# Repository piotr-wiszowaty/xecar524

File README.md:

xecar524
========

An [Atari XL/XE](http://en.wikipedia.org/wiki/Atari_8-bit_family) flash cartridge
with a battery backed up R-Time 8 emulator. The device handles up to 4 Mbit,
3.3V, PLCC-32 flash memories (e.g. SST39VF010, SST39VF020, SST39VF040).

By default the base SDX image at `$00000` is loaded. Another cartridge image
may be switched to by using `CAR` command.

ROM Memory Map
--------------

* `$00000`..`$1FFFF` - SpartaDOS X 4.49, 128k (SDX449\_sdx128.rom)
* `$20000`..`$23FFF` - 043M OSS cartridge (e.g. MAC/65 1.00)
* `$24000`..`$27FFF` - 034M OSS cartridge (e.g. MAC-65 v1.02)
* `$28000`..`$2BFFF` - standard 16k cartridge
* `$2C000`..`$2DFFF` - standard 8k cartridge

Cartridge Selection
-------------------

The cartridge image to switch to is selected with jumpers:

* `CFG0`: off, `CFG1`: off - 043M OSS cartridge
* `CFG0`: on,  `CFG1`: off - 034M OSS cartridge
* `CFG0`: off, `CFG1`: on  - standard 16k cartridge
* `CFG0`: on,  `CFG1`: on  - standard 8k cartridge

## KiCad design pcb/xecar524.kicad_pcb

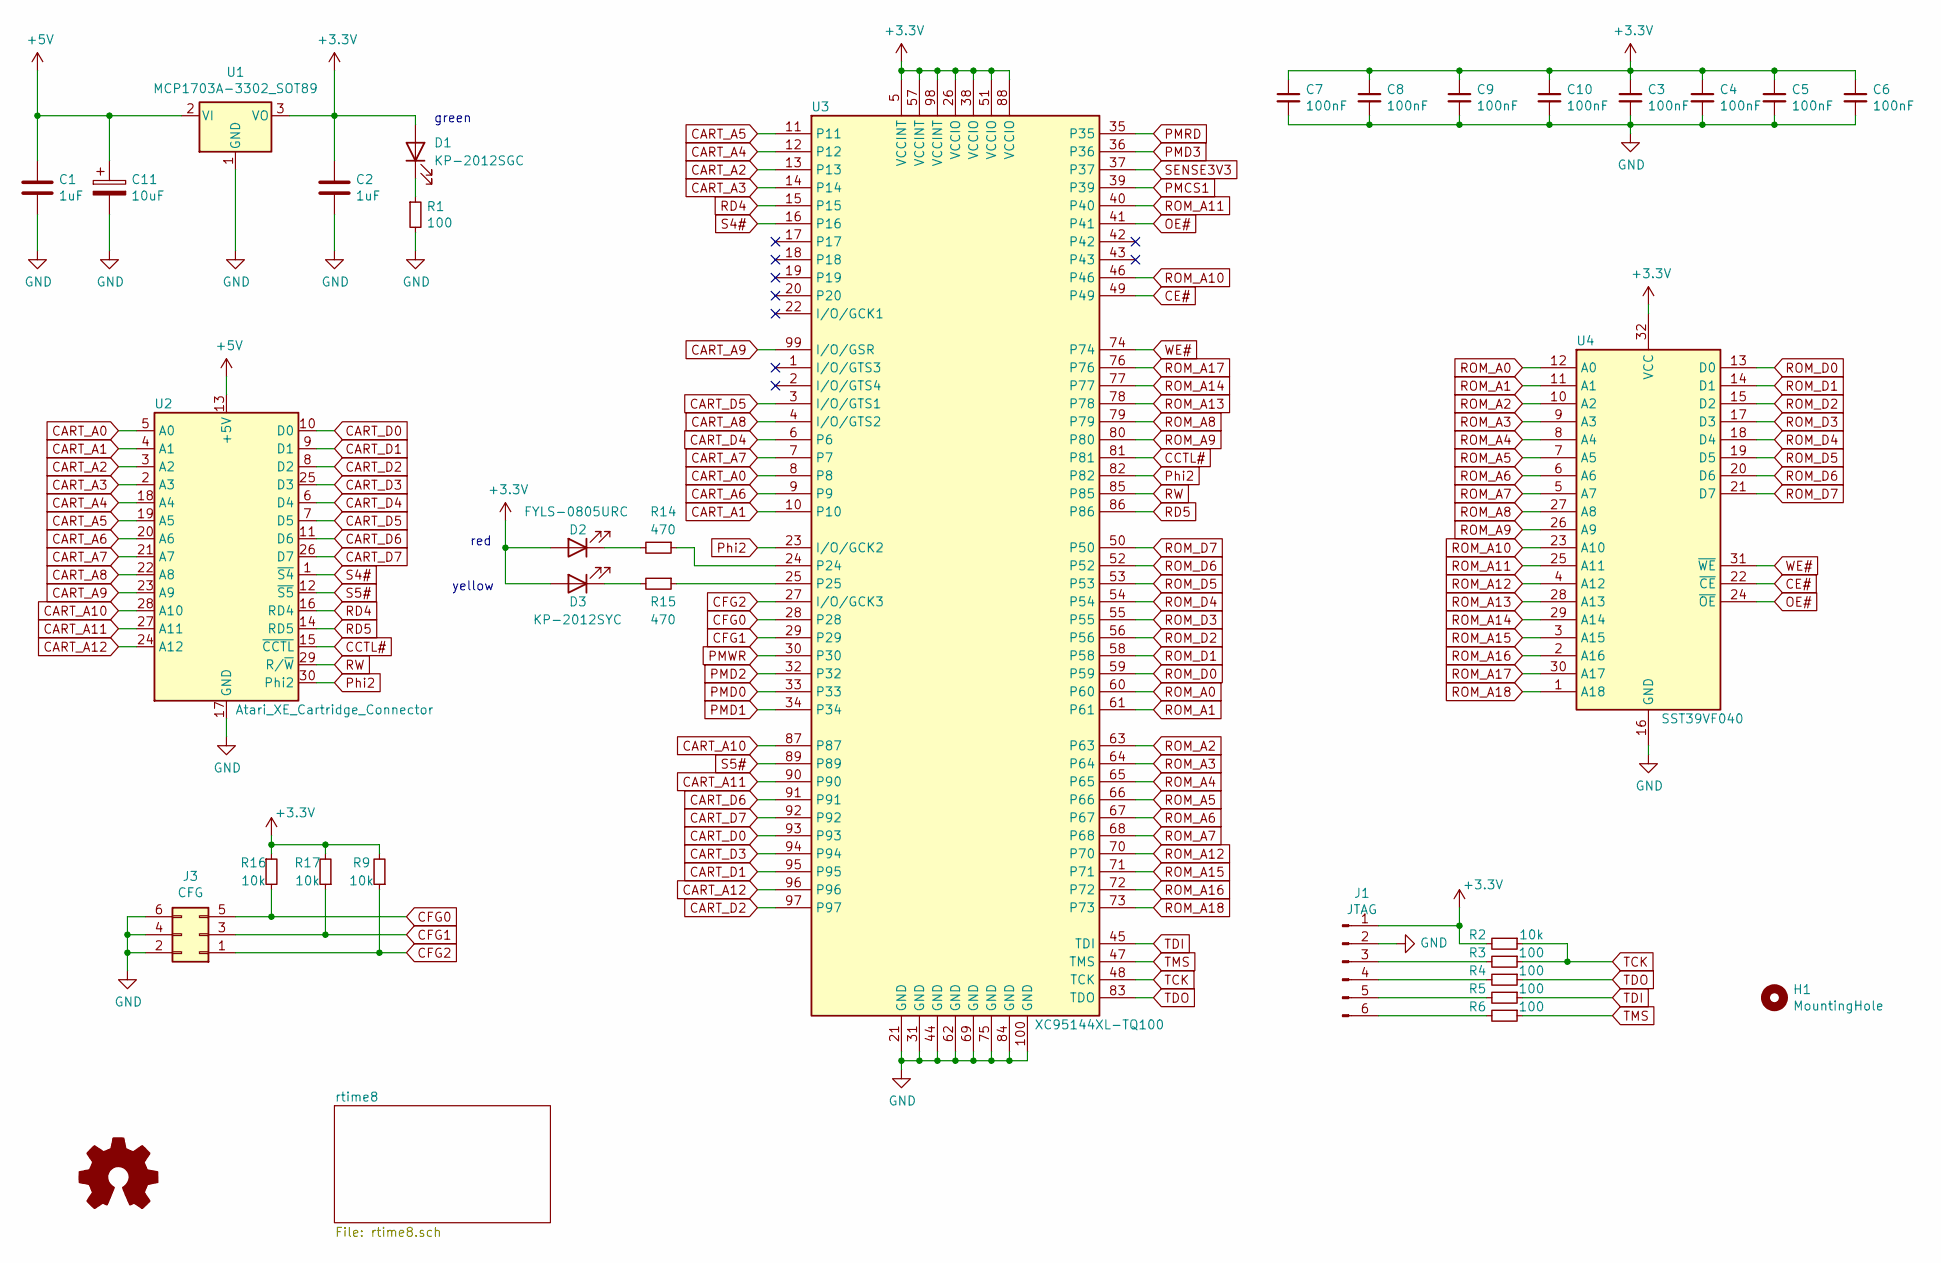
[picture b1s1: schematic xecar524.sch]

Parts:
C1, C2: 1uF; C_1206_3216Metric_Pad1.33x1.80mm_HandSolder
C3, C4, C5, C6, C7, C8, C9, C10: 100nF; C_0805_2012Metric_Pad1.18x1.45mm_HandSolder
C11: 10uF; CP_EIA-3528-12_Kemet-T_Pad1.50x2.35mm_HandSolder
D1: KP-2012SGC; D_0805_2012Metric_Pad1.15x1.40mm_HandSolder
D2: FYLS-0805URC; D_0805_2012Metric_Pad1.15x1.40mm_HandSolder
D3: KP-2012SYC; D_0805_2012Metric_Pad1.15x1.40mm_HandSolder
H1: MountingHole; MountingHole_5mm
J1: JTAG; PinHeader_1x06_P2.54mm_Horizontal_HighProfile
J3: CFG; PinHeader_2x03_P2.54mm_Horizontal
LOGO1: Logo_Open_Hardware_Small; OSHW-Symbol_8.9x8mm_Copper
R1, R3, R4, R5, R6: 100; R_0805_2012Metric_Pad1.20x1.40mm_HandSolder
R2, R9, R16, R17: 10k; R_0805_2012Metric_Pad1.20x1.40mm_HandSolder
R14, R15: 470; R_0805_2012Metric_Pad1.20x1.40mm_HandSolder
U1: MCP1703A-3302_SOT89; SOT-89-3
U2: Atari_XE_Cartridge_Connector
U3: XC95144XL-TQ100; TQFP-100_14x14mm_P0.5mm
U4: SST39VF040; PLCC-32_SMD-Socket

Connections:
+3V3: C2.1, C3.1, C4.1, C5.1, C6.1, C7.1, C8.1, C9.1, C10.1, D1.2 (A), D2.2 (A), D3.2 (A), J1.1, R2.2, R9.2, R16.1, R17.2, U1.3 (VO), U3.5 (VCCINT), U3.26 (VCCIO), U3.38 (VCCIO), U3.51 (VCCIO), U3.57 (VCCINT), U3.88 (VCCIO), U3.98 (VCCINT), U4.32 (VCC); also elsewhere on the board
+5V: C1.1, C11.1, U1.2 (VI), U2.13 (+5V)
CART_A0: U2.5 (A0), U3.8
CART_A1: U2.4 (A1), U3.10
CART_A2: U2.3 (A2), U3.13
CART_A3: U2.2 (A3), U3.14
CART_A4: U2.18 (A4), U3.12
CART_A5: U2.19 (A5), U3.11
CART_A6: U2.20 (A6), U3.9
CART_A7: U2.21 (A7), U3.7
CART_A8: U2.22 (A8), U3.4 (I/O/GTS2)
CART_A9: U2.23 (A9), U3.99 (I/O/GSR)
CART_A10: U2.28 (A10), U3.87
CART_A11: U2.27 (A11), U3.90
CART_A12: U2.24 (A12), U3.96
CART_D0: U2.10 (D0), U3.93
CART_D1: U2.9 (D1), U3.95
CART_D2: U2.8 (D2), U3.97
CART_D3: U2.25 (D3), U3.94
CART_D4: U2.6 (D4), U3.6
CART_D5: U2.7 (D5), U3.3 (I/O/GTS1)
CART_D6: U2.11 (D6), U3.91
CART_D7: U2.26 (D7), U3.92
CCTL#: U2.15 (~CCTL~), U3.81
CE#: U3.49, U4.22 (~CE~)
CFG0: J3.5, R16.2, U3.28
CFG1: J3.3, R17.1, U3.29
CFG2: J3.1, R9.1, U3.27 (I/O/GCK3)
GND: C1.2, C2.2, C3.2, C4.2, C5.2, C6.2, C7.2, C8.2, C9.2, C10.2, C11.2, J1.2, J3.2, J3.4, J3.6, R1.2, U1.1 (GND), U2.17 (GND), U3.21 (GND), U3.31 (GND), U3.44 (GND), U3.62 (GND), U3.69 (GND), U3.75 (GND), U3.84 (GND), U3.100 (GND), U4.16 (GND); also elsewhere on the board
unnamed: D1.1 (K), R1.1
unnamed: D2.1 (K), R14.2
unnamed: D3.1 (K), R15.2
unnamed: J1.3, R3.2
unnamed: J1.4, R4.2
unnamed: J1.5, R5.2
unnamed: J1.6, R6.2
unnamed: R14.1, U3.24
unnamed: R15.1, U3.25
OE#: U3.41, U4.24 (~OE~)
PMCS1: U3.39; also elsewhere on the board
PMD0: U3.33; also elsewhere on the board
PMD1: U3.34; also elsewhere on the board
PMD2: U3.32; also elsewhere on the board
PMD3: U3.36; also elsewhere on the board
PMRD: U3.35; also elsewhere on the board
PMWR: U3.30; also elsewhere on the board
Phi2: U2.30 (Phi2), U3.23 (I/O/GCK2), U3.82
RD4: U2.16 (RD4), U3.15
RD5: U2.14 (RD5), U3.86
ROM_A0: U3.60, U4.12 (A0)
ROM_A1: U3.61, U4.11 (A1)
ROM_A2: U3.63, U4.10 (A2)
ROM_A3: U3.64, U4.9 (A3)
ROM_A4: U3.65, U4.8 (A4)
ROM_A5: U3.66, U4.7 (A5)
ROM_A6: U3.67, U4.6 (A6)
ROM_A7: U3.68, U4.5 (A7)
ROM_A8: U3.79, U4.27 (A8)
ROM_A9: U3.80, U4.26 (A9)
ROM_A10: U3.46, U4.23 (A10)
ROM_A11: U3.40, U4.25 (A11)
ROM_A12: U3.70, U4.4 (A12)
ROM_A13: U3.78, U4.28 (A13)
ROM_A14: U3.77, U4.29 (A14)
ROM_A15: U3.71, U4.3 (A15)
ROM_A16: U3.72, U4.2 (A16)
ROM_A17: U3.76, U4.30 (A17)
ROM_A18: U3.73, U4.1 (A18)
ROM_D0: U3.59, U4.13 (D0)
ROM_D1: U3.58, U4.14 (D1)
ROM_D2: U3.56, U4.15 (D2)
ROM_D3: U3.55, U4.17 (D3)
ROM_D4: U3.54, U4.18 (D4)
ROM_D5: U3.53, U4.19 (D5)
ROM_D6: U3.52, U4.20 (D6)
ROM_D7: U3.50, U4.21 (D7)
RW: U2.29 (R/~W~), U3.85
S4#: U2.1 (~S4~), U3.16
S5#: U2.12 (~S5~), U3.89
SENSE3V3: U3.37; also elsewhere on the board
TCK: R2.1, R3.1, U3.48 (TCK)
TDI: R5.1, U3.45 (TDI)
TDO: R4.1, U3.83 (TDO)
TMS: R6.1, U3.47 (TMS)
WE#: U3.74, U4.31 (~WE~)

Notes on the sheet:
green
red
yellow

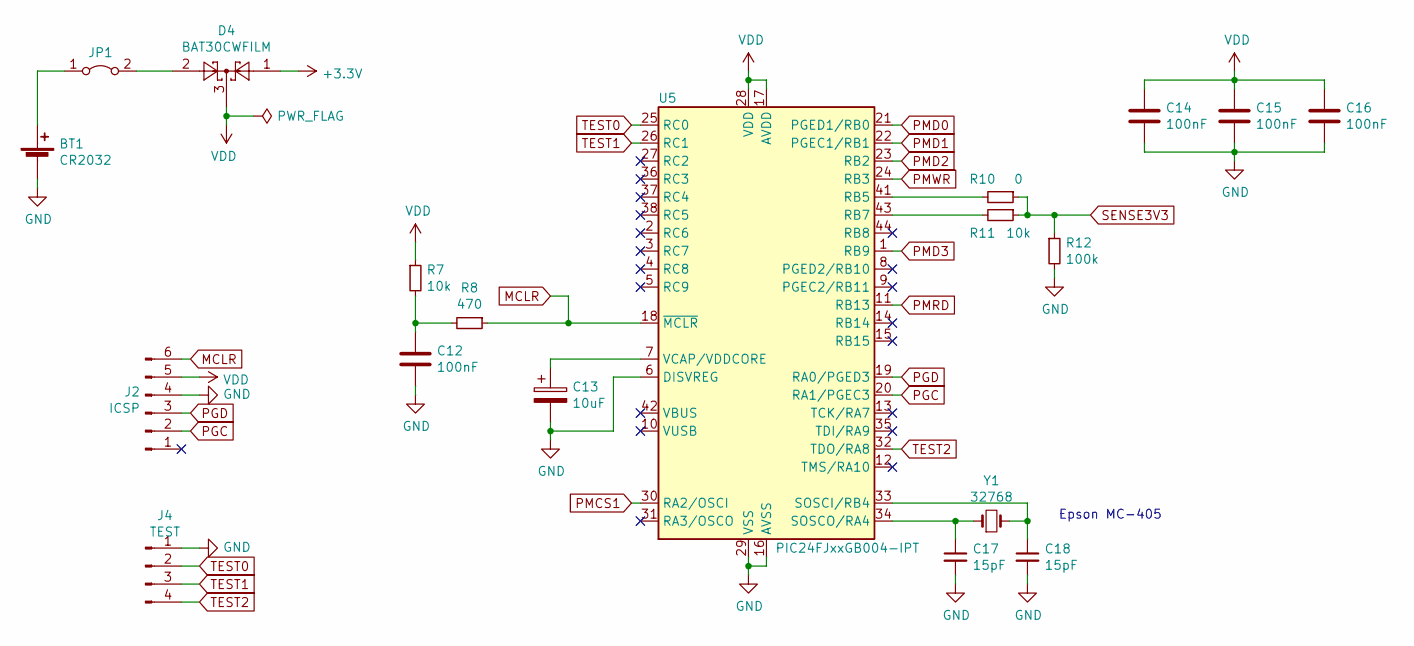
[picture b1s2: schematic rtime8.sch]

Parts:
BT1: CR2032; BatteryHolder_Connfly_DS1092-10
C12, C14, C15, C16: 100nF; C_0805_2012Metric_Pad1.18x1.45mm_HandSolder
C13: 10uF; CP_EIA-3528-12_Kemet-T_Pad1.50x2.35mm_HandSolder
C17, C18: 15pF; C_0805_2012Metric_Pad1.18x1.45mm_HandSolder
D4: BAT30CWFILM; SOT-323_SC-70_Handsoldering
J2: ICSP; PinHeader_1x06_P2.54mm_Horizontal_HighProfile
J4: TEST; PinHeader_1x04_P2.54mm_Vertical
JP1: Jumper_2_Bridged; PinHeader_1x02_P2.54mm_Vertical
R7, R11: 10k; R_0805_2012Metric_Pad1.20x1.40mm_HandSolder
R8: 470; R_0805_2012Metric_Pad1.20x1.40mm_HandSolder
R10: 0; R_0805_2012Metric_Pad1.20x1.40mm_HandSolder
R12: 100k; R_0805_2012Metric_Pad1.20x1.40mm_HandSolder
U5: PIC24FJxxGB004-IPT; TQFP-44_10x10mm_P0.8mm
Y1: 32768; Crystal_SMD_SeikoEpson_MC406-4Pin_9.6x4.1mm_HandSoldering

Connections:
+3V3: D4.1; also elsewhere on the board
GND: BT1.2 (-), C12.2, C13.2, C14.2, C15.2, C16.2, C17.2, C18.2, J2.4, J4.1, R12.2, U5.6 (DISVREG), U5.16 (AVSS), U5.29 (VSS), U5.39 (VSS); also elsewhere on the board
MCLR: J2.6, R8.1, U5.18 (~MCLR~)
unnamed: BT1.1 (+), JP1.1 (A)
unnamed: C12.1, R7.2, R8.2
unnamed: C13.1, U5.7 (VCAP/VDDCORE)
unnamed: C17.1, U5.34 (SOSCO/RA4), Y1.1, Y1.4
unnamed: C18.1, U5.33 (SOSCI/RB4), Y1.2, Y1.3
unnamed: D4.2, JP1.2 (B)
unnamed: R10.2, U5.41 (RB5)
unnamed: R11.2, U5.43 (RB7)
PGC: J2.2, U5.20 (RA1/PGEC3)
PGD: J2.3, U5.19 (RA0/PGED3)
PMCS1: U5.30 (RA2/OSCI); also elsewhere on the board
PMD0: U5.21 (PGED1/RB0); also elsewhere on the board
PMD1: U5.22 (PGEC1/RB1); also elsewhere on the board
PMD2: U5.23 (RB2); also elsewhere on the board
PMD3: U5.1 (RB9); also elsewhere on the board
PMRD: U5.11 (RB13); also elsewhere on the board
PMWR: U5.24 (RB3); also elsewhere on the board
SENSE3V3: R10.1, R11.1, R12.1; also elsewhere on the board
TEST0: J4.2, U5.25 (RC0)
TEST1: J4.3, U5.26 (RC1)
TEST2: J4.4, U5.32 (TDO/RA8)
VDD: C14.1, C15.1, C16.1, D4.3, J2.5, R7.1, U5.17 (AVDD), U5.28 (VDD), U5.40 (VDD)

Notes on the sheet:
Epson MC-405

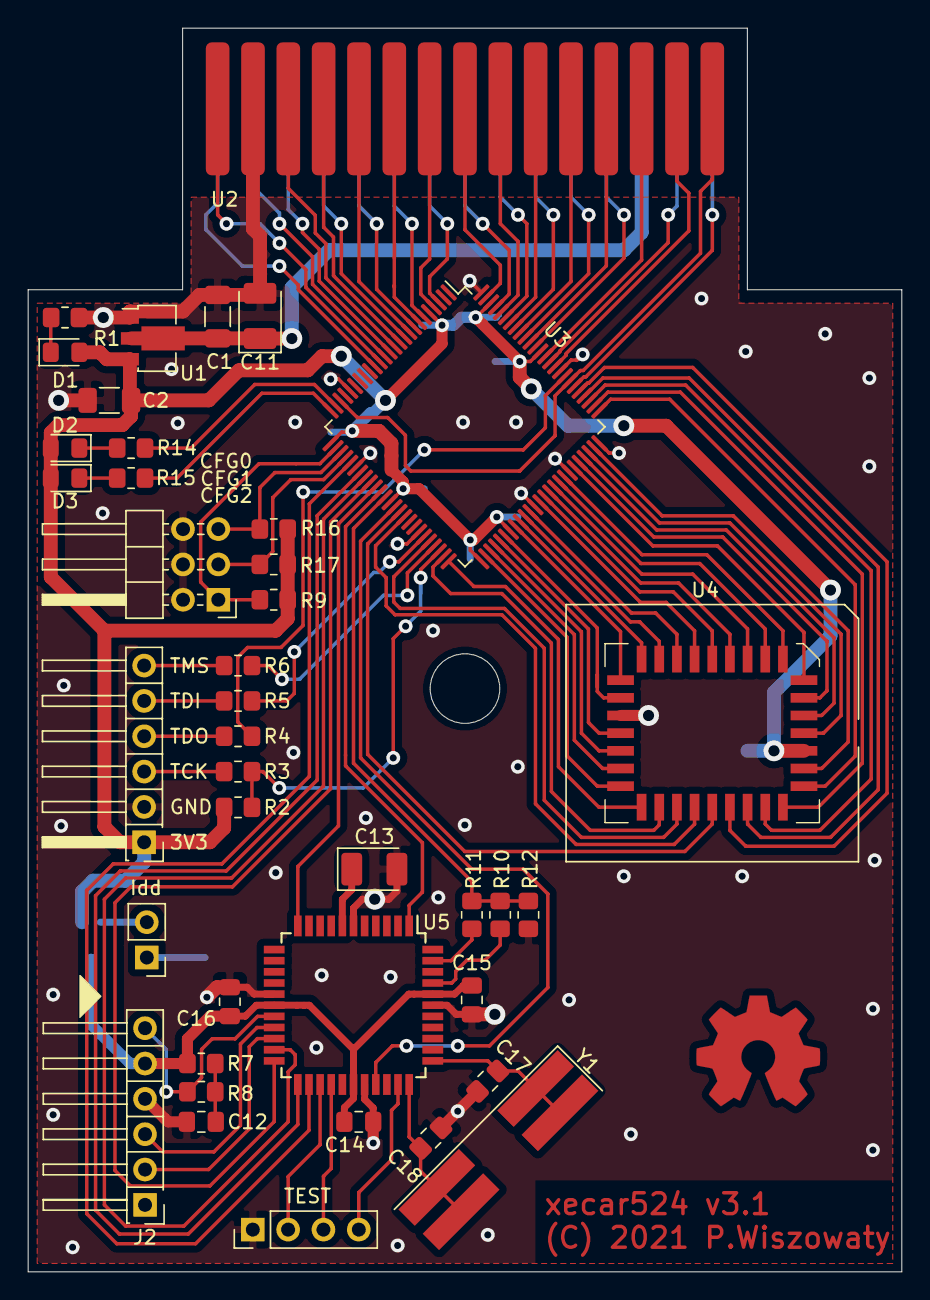
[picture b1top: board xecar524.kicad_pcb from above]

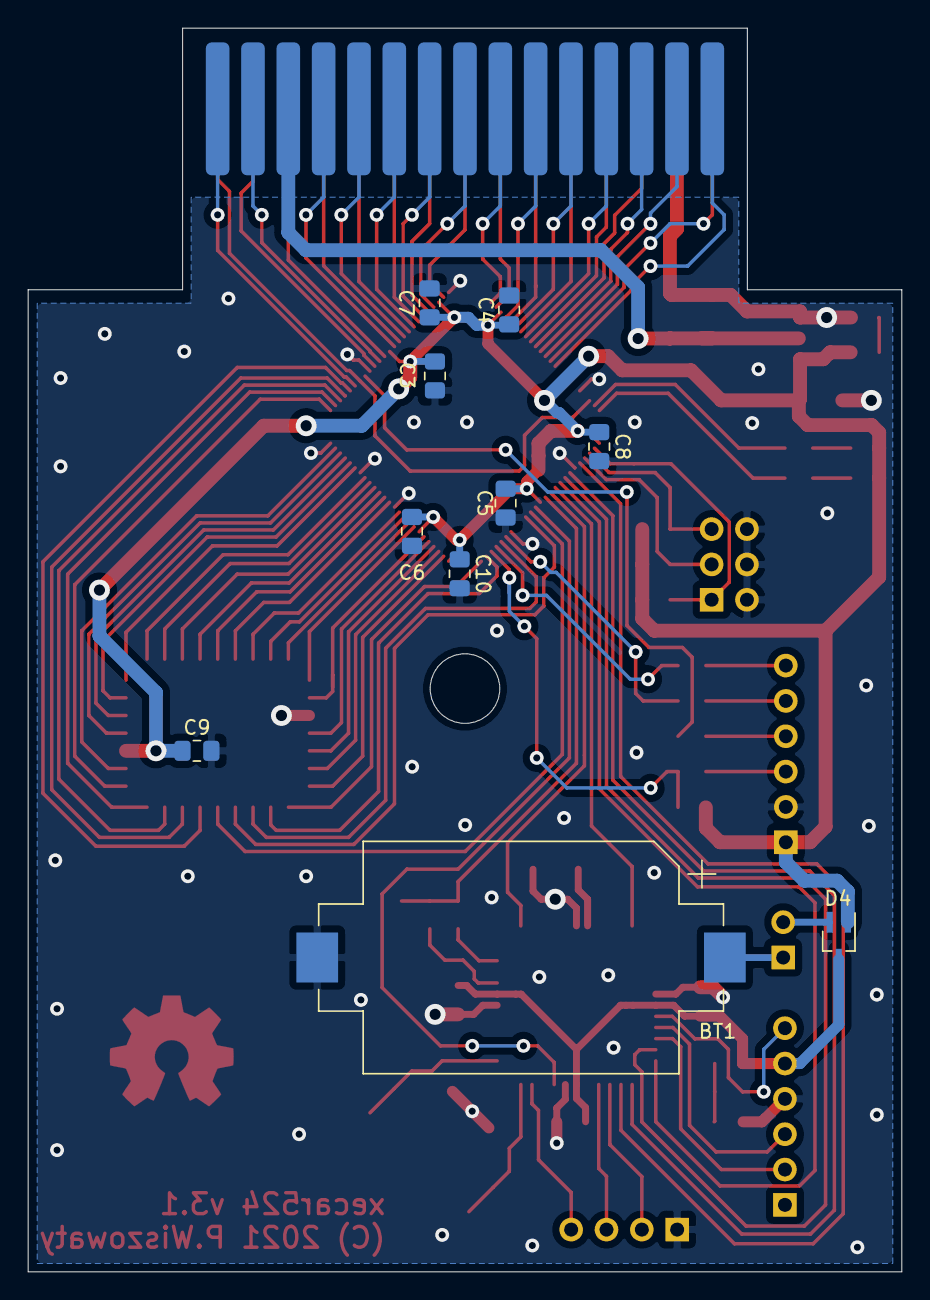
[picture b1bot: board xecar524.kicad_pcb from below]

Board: 2 copper layers, 62.8 x 89.4 mm, 52 parts (10 on the bottom side), 100 nets.

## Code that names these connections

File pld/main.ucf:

#NET "phi2" LOC = "P82";
NET "phi2" LOC = "P23";
NET "r_w" LOC = "P85";
NET "rd4" LOC = "P15";
NET "rd5" LOC = "P86";
NET "s4_n" LOC = "P16";
NET "s5_n" LOC = "P89";
NET "cctl_n" LOC = "P81";
NET "cart_d<0>" LOC = "P93";
NET "cart_d<1>" LOC = "P95";
NET "cart_d<2>" LOC = "P97";
NET "cart_d<3>" LOC = "P94";
NET "cart_d<4>" LOC = "P6";
NET "cart_d<5>" LOC = "P3";
NET "cart_d<6>" LOC = "P91";
NET "cart_d<7>" LOC = "P92";
NET "cart_a<0>" LOC = "P8";
NET "cart_a<1>" LOC = "P10";
NET "cart_a<2>" LOC = "P13";
NET "cart_a<3>" LOC = "P14";
NET "cart_a<4>" LOC = "P12";
NET "cart_a<5>" LOC = "P11";
NET "cart_a<6>" LOC = "P9";
NET "cart_a<7>" LOC = "P7";
NET "cart_a<8>" LOC = "P4";
NET "cart_a<9>" LOC = "P99";
NET "cart_a<10>" LOC = "P87";
NET "cart_a<11>" LOC = "P90";
NET "cart_a<12>" LOC = "P96";

NET "we_n" LOC = "P74";
NET "oe_n" LOC = "P41";
NET "ce_n" LOC = "P49";
NET "rom_d<0>" LOC = "P59";
NET "rom_d<1>" LOC = "P58";
NET "rom_d<2>" LOC = "P56";
NET "rom_d<3>" LOC = "P55";
NET "rom_d<4>" LOC = "P54";
NET "rom_d<5>" LOC = "P53";
NET "rom_d<6>" LOC = "P52";
NET "rom_d<7>" LOC = "P50";
NET "rom_a<0>" LOC = "P60";
NET "rom_a<1>" LOC = "P61";
NET "rom_a<2>" LOC = "P63";
NET "rom_a<3>" LOC = "P64";
NET "rom_a<4>" LOC = "P65";
NET "rom_a<5>" LOC = "P66";
NET "rom_a<6>" LOC = "P67";
NET "rom_a<7>" LOC = "P68";
NET "rom_a<8>" LOC = "P79";
NET "rom_a<9>" LOC = "P80";
NET "rom_a<10>" LOC = "P46";
NET "rom_a<11>" LOC = "P40";
NET "rom_a<12>" LOC = "P70";
NET "rom_a<13>" LOC = "P78";
NET "rom_a<14>" LOC = "P77";
NET "rom_a<15>" LOC = "P71";
NET "rom_a<16>" LOC = "P72";
NET "rom_a<17>" LOC = "P76";
NET "rom_a<18>" LOC = "P73";

NET "pmcs1" LOC = "P39";
NET "pmwr" LOC = "P30";
NET "pmrd" LOC = "P35";
NET "pmd<0>" LOC = "P33";
NET "pmd<1>" LOC = "P34";
NET "pmd<2>" LOC = "P32";
NET "pmd<3>" LOC = "P36";
NET "sense3v3" LOC = "P37";

NET "cfg0" LOC = "P28";
NET "cfg1" LOC = "P29";
NET "cfg2" LOC = "P27";

NET "led_r" LOC = "P24";
NET "led_y" LOC = "P25";

NET "phi2" TNM_NET = phi2;
TIMESPEC TS_phi2 = PERIOD "phi2" 562 ns HIGH 250 ns;

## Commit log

2021-06-13 Add PCB design files
2021-06-13 PCB: Add top GND copper pour
2021-06-13 PCB: Tweak some tracks
2021-06-13 PCB: Tweak tracks
2021-06-13 PCB: Tweak electrical schematic
2021-06-14 PCB: Add CAM files
2021-06-17 PCB: Tweak one track
2021-06-29 PCB: Widen some power tracks
2021-06-29 PCB: Shrink cartridge connector
2021-07-04 PCB: Update LEDs and their current-setting resistors
2021-07-04 PCB: Exchange cfg signals
2021-07-04 PCB: Decrease yellow LED brightness
2021-07-05 Add PLD design files
2021-07-07 PCB: Resize
2021-07-11 PLD: Turn on message filtering
2021-07-16 Add R-Time 8 emulator
2021-07-17 PCB, PLD: Integrate R-Time 8 emulator
2021-07-17 PCB: Add connector for measuring deep sleep current
2021-07-17 PCB: Add description to deep sleep current measurement connector, add OSHW symbol
2021-07-17 PCB: Move ICSP connector marker
2021-07-17 PCB: Add OSHW symbol on schematic
2021-07-17 PCB: Enlarge a GND via
2021-07-17 PCB: Add test connector
2021-07-17 PCB: Add quartz crystal description
2021-07-17 PCB: Move description
2021-07-18 PCB, PLD: Add one configuration jumper
2021-07-18 PLD: Remove redundant pin constraint
2021-07-18 PCB, PLD: Add a connection between PLD and microcontroller
2021-07-18 Tweak connections between PLD and uC
2021-07-19 PLD: Handle only SDX128
2021-07-20 PLD: Handle OSS carts; handle standard 8k carts
2021-07-23 PLD: Handle OSS cart with 034M bank order
2021-07-24 PLD: Handle standard 16k cartridges
2021-08-10 PCB: Add connection for detecting power loss
2021-08-13 PLD: Update pin assignments
2021-08-13 PLD: Handle OSS cartridges
2021-08-15 R-Time8: Migrate to PIC24FJ32GA004
2021-09-12 Switch to PIC24FJ64GB004 as RTime8 emulator
2021-09-12 PCB: Update CAM files
2021-09-14 PCB: Add photos of the device
2021-09-14 PCB: Correct file name

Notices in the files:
pcb/xecar524.kicad_pcb:
(C) 2021 P.Wiszowaty
